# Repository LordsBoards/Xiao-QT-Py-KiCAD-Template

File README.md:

# QT Py/Xiao Board Footprint Template for KiCad

This KiCad template provides a footprint for the QT Py/Xiao board from Seeed. The template includes:

- **Mounting Pins:** Accurate locations.
- **USB-C Port:** Position and orientation.
- **Mechanical Dimensions:** Exact measurements.
- **Pinout:** All pins are clearly labeled for easy reference.

## How to Use

1. Clone or download this repository.
2. Open KiCad and import the footprint file.
3. Utilize the QT Py/Xiao footprint in your design.

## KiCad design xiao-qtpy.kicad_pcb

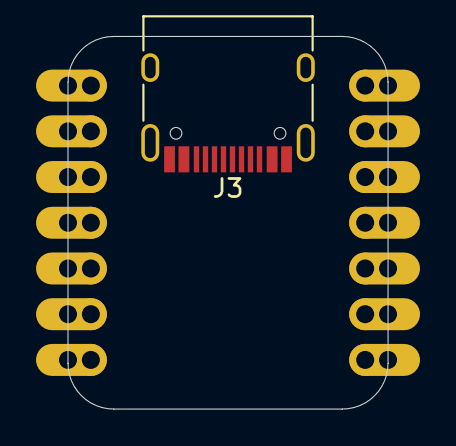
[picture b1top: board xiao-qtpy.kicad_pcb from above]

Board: 2 copper layers, 17.8 x 20.7 mm, 3 parts (0 on the bottom side), 2 nets, no tracks yet.

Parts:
J1: Xiao Left; Conn_01x_07_Xiao
J2: Xiao Right; Conn_01x_07_Xiao
J3: USB_C_Receptacle_USB2.0; USB_C_Receptacle_HRO_TYPE-C-31-M-12

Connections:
GND: J2.6, J3.A1 (GND), J3.A12 (GND), J3.B1 (GND), J3.B12 (GND)
unnamed: J3.A4 (VBUS), J3.A9 (VBUS), J3.B4 (VBUS), J3.B9 (VBUS)

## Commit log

2023-08-07 Added readme
2023-08-07 Added image
